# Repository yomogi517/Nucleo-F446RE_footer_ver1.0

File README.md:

## 使用時の注意
BNO055のフットプリントが電源とI2Cのピン側はあっていますが、INT,RESET,Voutなどのピン配が異なります。

基板外側のピンソケットのみ接続してください。

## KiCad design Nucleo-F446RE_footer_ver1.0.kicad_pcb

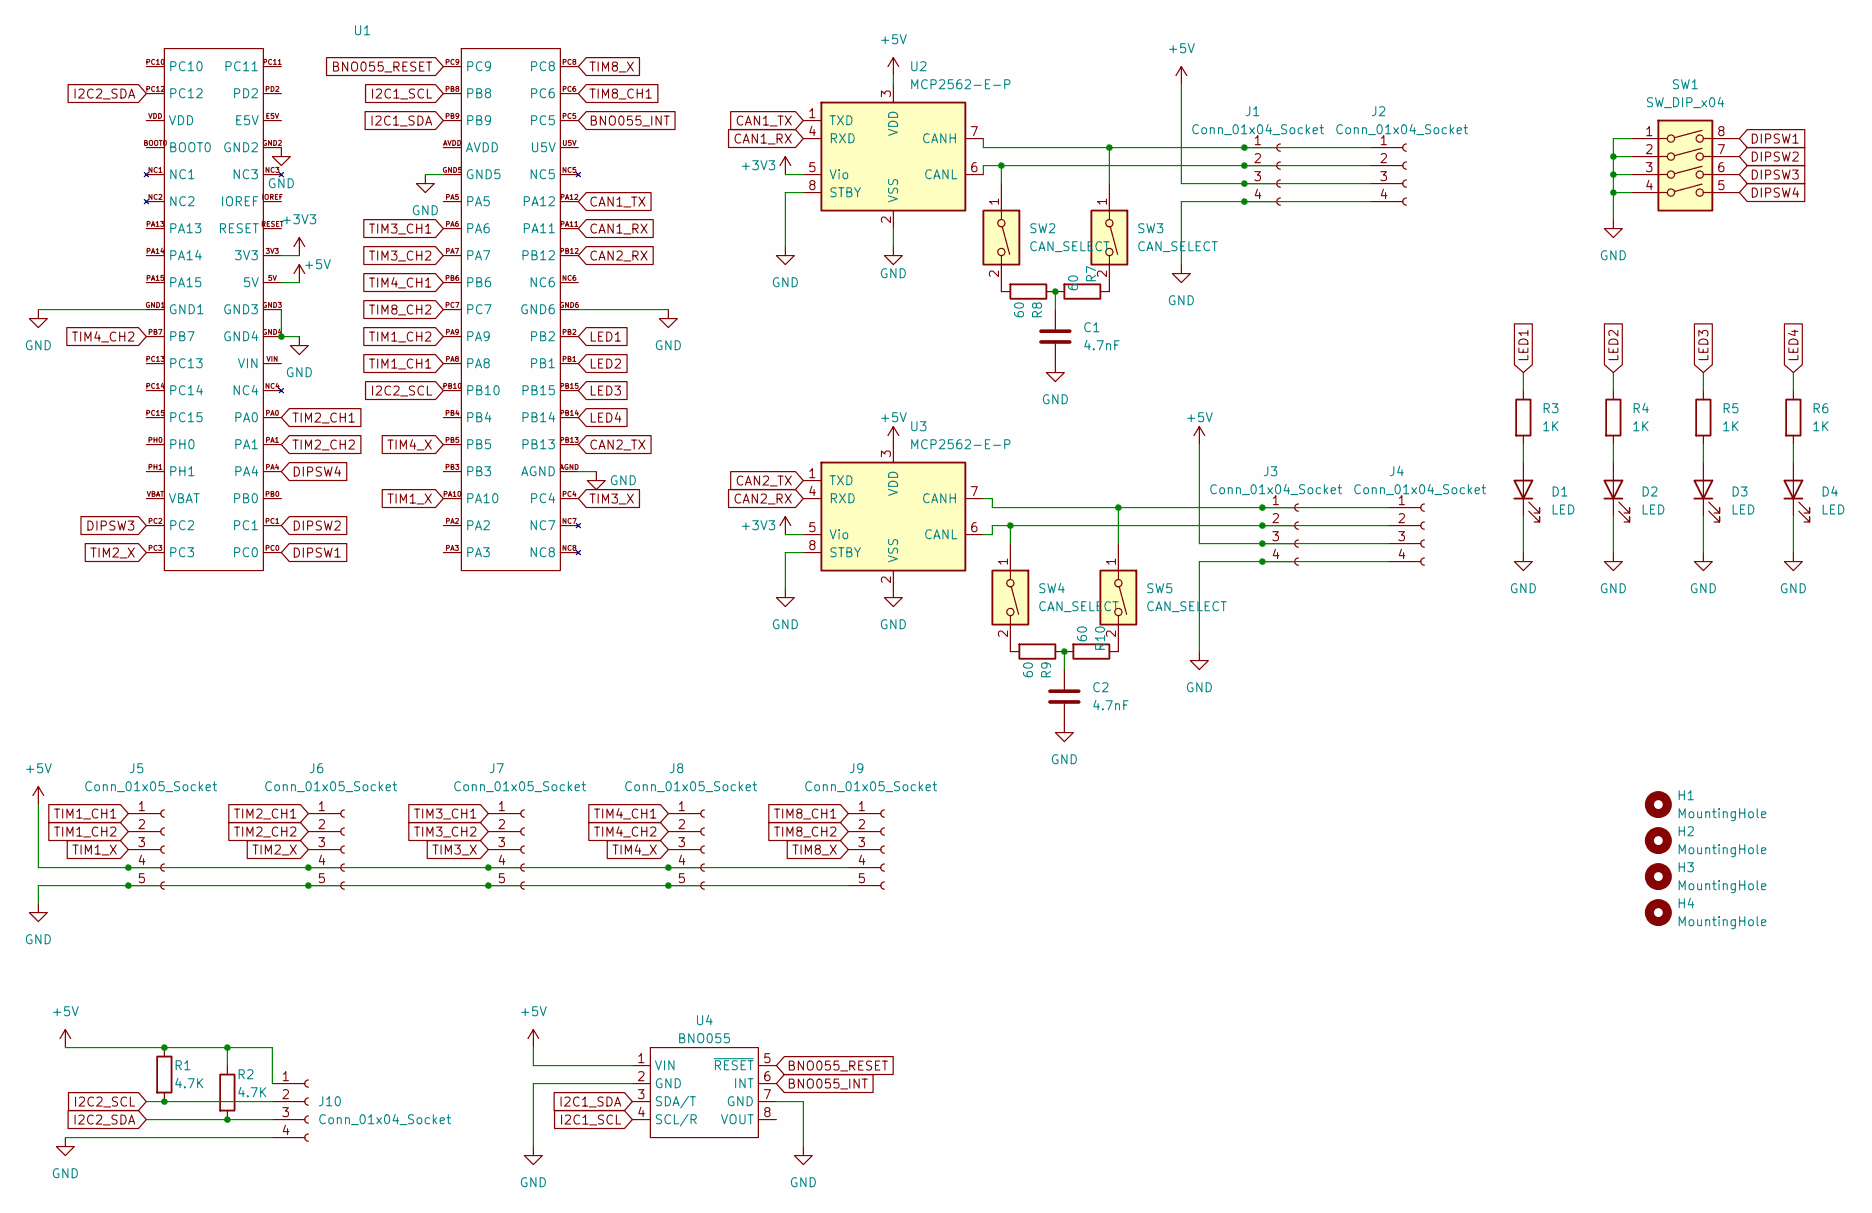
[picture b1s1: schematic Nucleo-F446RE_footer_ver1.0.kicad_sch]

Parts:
C1, C2: 4.7nF; C_Disc_D4.3mm_W1.9mm_P5.00mm
D1, D2, D3, D4: LED; LED_D3.0mm
H1, H2, H3, H4: MountingHole; MountingHole_3.2mm_M3
J1, J2, J3, J4: Conn_01x04_Socket; JST_XA_S04B-XASK-1_1x04_P2.50mm_Horizontal
J5, J6, J7, J8, J9: Conn_01x05_Socket; JST_XA_B05B-XASK-1_1x05_P2.50mm_Vertical
J10: Conn_01x04_Socket; JST_XA_B04B-XASK-1_1x04_P2.50mm_Vertical
R1, R2: 4.7K; R_Axial_DIN0207_L6.3mm_D2.5mm_P7.62mm_Horizontal
R3, R4, R5, R6: 1K; R_Axial_DIN0207_L6.3mm_D2.5mm_P7.62mm_Horizontal
R7, R8, R9, R10: 60; R_Axial_DIN0204_L3.6mm_D1.6mm_P7.62mm_Horizontal
SW1: SW_DIP_x04; DIP-8_W7.62mm
SW2, SW3, SW4, SW5: CAN_SELECT; PinHeader_1x02_P2.54mm_Vertical
U1: Nucleo64
U2, U3: MCP2562-E-P; DIP-8_W7.62mm
U4: BNO055; BNO055_akituki

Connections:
+3V3: U1.3V3, U2.5 (Vio), U3.5 (Vio)
+5V: J1.3, J2.3, J3.3, J4.3, J5.4, J6.4, J7.4, J8.4, J9.4, J10.1, R1.1, R2.1, U1.5V, U2.3 (VDD), U3.3 (VDD), U4.1 (VIN)
BNO055_INT: U1.PC5, U4.6 (INT)
BNO055_RESET: U1.PC9, U4.5 (~RESET)
CAN1_RX: U1.PA11, U2.4 (RXD)
CAN1_TX: U1.PA12, U2.1 (TXD)
CAN2_RX: U1.PB12, U3.4 (RXD)
CAN2_TX: U1.PB13, U3.1 (TXD)
DIPSW1: SW1.8, U1.PC0
DIPSW2: SW1.7, U1.PC1
DIPSW3: SW1.6, U1.PC2
DIPSW4: SW1.5, U1.PA4
GND: C1.2, C2.2, D1.1 (K), D2.1 (K), D3.1 (K), D4.1 (K), J1.4, J2.4, J3.4, J4.4, J5.5, J6.5, J7.5, J8.5, J9.5, J10.4, SW1.1, SW1.2, SW1.3, SW1.4, U1.AGND, U1.GND1, U1.GND2, U1.GND3, U1.GND4, U1.GND5, U1.GND6, U2.2 (VSS), U2.8 (STBY), U3.2 (VSS), U3.8 (STBY), U4.2 (GND), U4.7 (GND)
I2C1_SCL: U1.PB8, U4.4 (SCL/R)
I2C1_SDA: U1.PB9, U4.3 (SDA/T)
I2C2_SCL: J10.2, R1.2, U1.PB10
I2C2_SDA: J10.3, R2.2, U1.PC12
LED1: R3.1, U1.PB2
LED2: R4.1, U1.PB1
LED3: R5.1, U1.PB15
LED4: R6.1, U1.PB14
unnamed: C1.1, R7.2, R8.1
unnamed: C2.1, R9.1, R10.2
unnamed: D1.2 (A), R3.2
unnamed: D2.2 (A), R4.2
unnamed: D3.2 (A), R5.2
unnamed: D4.2 (A), R6.2
unnamed: J1.1, J2.1, SW3.1, U2.7 (CANH)
unnamed: J1.2, J2.2, SW2.1, U2.6 (CANL)
unnamed: J3.1, J4.1, SW5.1, U3.7 (CANH)
unnamed: J3.2, J4.2, SW4.1, U3.6 (CANL)
unnamed: R7.1, SW3.2
unnamed: R8.2, SW2.2
unnamed: R9.2, SW4.2
unnamed: R10.1, SW5.2
TIM1_CH1: J5.1, U1.PA8
TIM1_CH2: J5.2, U1.PA9
TIM1_X: J5.3, U1.PA10
TIM2_CH1: J6.1, U1.PA0
TIM2_CH2: J6.2, U1.PA1
TIM2_X: J6.3, U1.PC3
TIM3_CH1: J7.1, U1.PA6
TIM3_CH2: J7.2, U1.PA7
TIM3_X: J7.3, U1.PC4
TIM4_CH1: J8.1, U1.PB6
TIM4_CH2: J8.2, U1.PB7
TIM4_X: J8.3, U1.PB5
TIM8_CH1: J9.1, U1.PC6
TIM8_CH2: J9.2, U1.PC7
TIM8_X: J9.3, U1.PC8

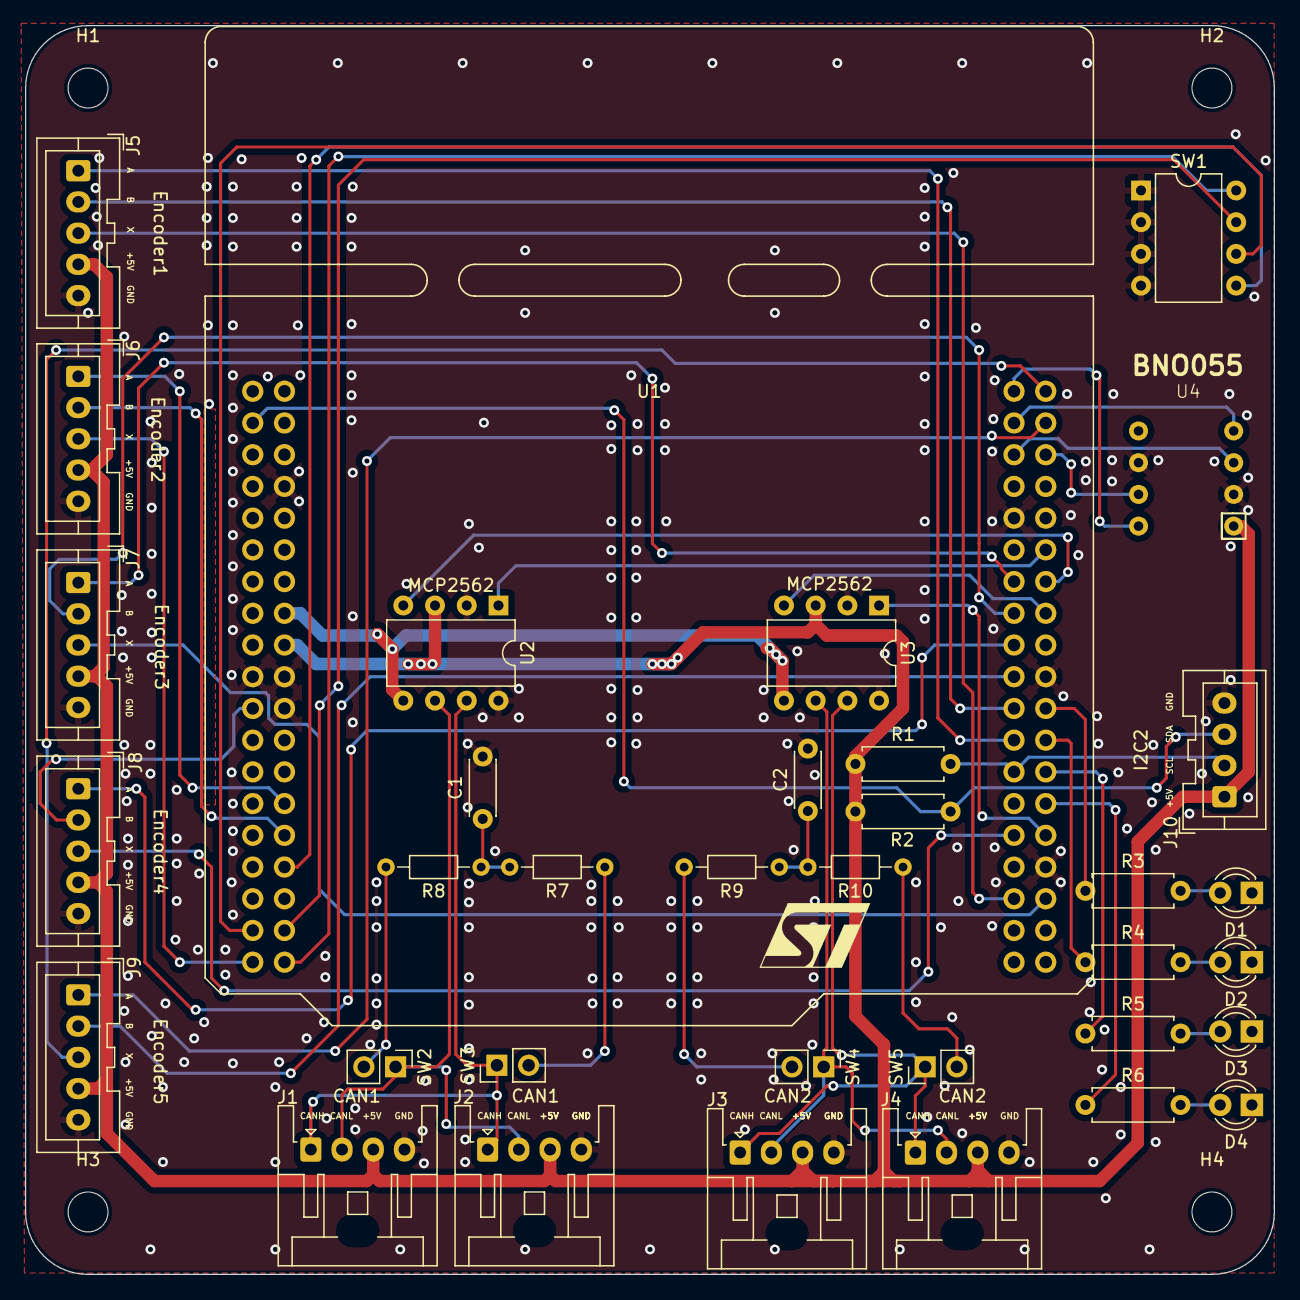
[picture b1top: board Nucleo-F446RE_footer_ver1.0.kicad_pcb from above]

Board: 2 copper layers, 100.0 x 100.0 mm, 39 parts (0 on the bottom side), 50 nets.

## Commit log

2024-04-28 add README
2024-04-28 add PDF
2024-04-28 add ピンアサイン
2025-01-08 [Add]gitignore
2025-01-08 [Update]README
